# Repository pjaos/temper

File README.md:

# Temper

A Python tool for discovering temperature and humidity sensor units on the local LAN, recording their readings to a SQLite database, and visualising the data through a web-based dashboard.

---

## Overview

Temper consists of two programs that work together along with the ESP32 based hardware.

- **`temper_db`** — a background collector that listens for sensor broadcasts on the LAN and saves every reading to a local SQLite database.
- **`temper_gui`** — a browser-based dashboard (built with [NiceGUI](https://nicegui.io) and [Plotly](https://plotly.com/python/)) for plotting temperature and humidity data across any time range.

The two programs are independent. `temper_db` can run continuously as a background service while `temper_gui` is started on demand to view the data.

---

## Hardware

Temper is designed to work with TEMPER-branded sensor units that broadcast JSON payloads over UDP on the local network. Each unit reports up to four independent temperature/humidity sensor channels, along with system telemetry (RAM, disk, uptime, RSSI, battery voltage, etc.).

Details of the hardware including kicad schematic, PCB and BOM can be found in the hardware folder.

This hardware runs a micropython program which can be found in software/mcu folder. It listens on **UDP port 2934** and responds to *Are You There* broadcast messages with the status (temperature/humidity etc).

---

## Requirements

- Python 3.10 or later

---

## Installation

The python wheel installer file can be found in the linux folder.

### Using the bundled installer

```bash
python3 install.py linux/temper-<version>-py3-none-any.whl
```

This creates a virtual environment, installs all dependencies, and adds the `temper_db` and `temper_gui` commands to your PATH. A temper_gui launch icon is also added to you desktop.

---

## Usage

### Collector — `temper_db`

Discovers TEMPER hardware units on the local LAN and writes every received reading to the database.

```bash
python -m temper.temper_db [options]
```

| Option | Description |
|---|---|
| `-d`, `--debug` | Enable debug logging (prints each received JSON payload). |
| `-a ADDRESS`, `--address ADDRESS` | Only record data from the unit at this IP address. If omitted, all units found are recorded. |
| `-s SECONDS`, `--seconds SECONDS` | Interval between *Are You There* broadcasts (default: 10 s). |
| `--enable_auto_start` | Register the tool to start on system boot |
| `--disable_auto_start` | Un-register the tool to start on system boot |
| `--check_auto_start` | Check the running status |

**Example — record all units, broadcast every 30 seconds:**

```bash
temper_db --seconds 30
```

**Example — record only one unit:**

```bash
temper_db --address 192.168.0.99
```

**Example Running as a service**

Use the built-in boot manager to have the tool start automatically (Linux only):

```bash
temper_db --seconds 30 --enable_auto_start
```

Press **Ctrl-C** to stop.

### Dashboard — `temper_gui`

Starts a local web server and opens the dashboard in the default browser.

```bash
temper_gui [options]
```

| Option | Description |
|---|---|
| `-d`, `--debug` | Enable debug logging. |
| `-p PORT`, `--port PORT` | TCP port for the NiceGUI web server (default: 8085). |
| `-n`, `--no_web_launch` | Start the server without opening a browser tab automatically. |
| `--enable_auto_start` | Register the tool to start on system boot |
| `--disable_auto_start` | Un-register the tool to start on system boot |
| `--check_auto_start` | Check the running status |

**Browser Example**

**Example — start on a non-default port:**

```bash
temper_gui --port 9090
```

**Example — headless server (access from another device):**

```bash
temper_gui --no_web_launch
```

Then navigate to `http://<host-ip>:8085` from any browser on the same network, including a mobile phone.

**Example Running as a service**

Use the built-in boot manager to have the tool start automatically (Linux only):

```bash
temper_gui -n --enable_auto_start
```

---

## Dashboard features

The dashboard is responsive and works on both desktop and mobile browsers.

**Sidebar controls**

- **Units** — chips showing every known unit and its total reading count. Click to select a unit and load its data.
- **Time Range** — preset buttons (1h, 6h, 24h, 7 days, 30 days, All) plus a Custom option with date pickers.
- **Plot** — switch between Temperature and Humidity views.
- **Sensor Names** — rename each of the four sensor channels (e.g. *Living Room*, *Loft*, *Outside*). Names are saved to `sensor_names.json` and persist across restarts. The chart legend and stat tiles update immediately on save.

**Main area**

- **Latest Reading** — a tile grid showing the most recent temperature and humidity value for each active sensor on the selected unit.
- **Chart** — an interactive Plotly time-series plot. Hover over any point to see values for all sensors at that timestamp. Zoom and pan with standard Plotly controls.

---

## Data storage

The database and sensor name configuration are stored in:

| Platform | Path |
|---|---|
| Linux / macOS (XDG) | `~/.config/temper/` |
| Linux / macOS (fallback) / Windows | `~/.temper/` |

Files created:

| File | Contents |
|---|---|
| `temper_sensor_data.db` | SQLite database containing all sensor readings. |
| `sensor_names.json` | User-defined display names for the four sensor channels. |

### Database schema

Two tables are used:

**`units`** — one row per discovered device.

| Column | Type | Description |
|---|---|---|
| `id` | INTEGER | Primary key. |
| `unit_name` | TEXT | Unique device identifier (e.g. `TEMPER_DEV`). |
| `device_type` | TEXT | Always `SENSOR` for TEMPER hardware. |
| `product_id` | TEXT | Always `TEMPER`. |
| `ip_address` | TEXT | Last seen IP address. |
| `os` | TEXT | Firmware OS (e.g. `MicroPython`). |
| `group_name` | TEXT | Optional group label from the device. |
| `service_list` | TEXT | Services advertised by the device. |
| `first_seen` | TIMESTAMP | UTC timestamp of first contact. |
| `last_seen` | TIMESTAMP | UTC timestamp of most recent contact. |

**`sensor_readings`** — one row per received broadcast.

| Column | Type | Description |
|---|---|---|
| `id` | INTEGER | Primary key. |
| `unit_id` | INTEGER | Foreign key → `units.id`. |
| `recorded_at` | TIMESTAMP | UTC time the reading was received. |
| `rx_time_secs` | REAL | Unix timestamp from the device itself. |
| `uptime_seconds` | INTEGER | Device uptime in seconds. |
| `sensor_1_temp` … `sensor_4_temp` | REAL | Temperature readings in °C. |
| `sensor_1_humidity` … `sensor_4_humidity` | REAL | Relative humidity readings in %RH. |
| `param_3v3` | REAL | 3.3 V rail voltage. |
| `param_vbat` | REAL | Battery voltage. |
| `param_rssi` | REAL | Wi-Fi signal strength in dBm. |
| `param_board_temp` | REAL | On-board temperature sensor reading. |
| `ram_*`, `disk_*` | INTEGER | RAM and disk usage telemetry. |

### Maintenance

To delete readings older than 90 days from a Python session:

```python
from temper.temper_db import TemperDB
from unittest.mock import MagicMock
db = TemperDB.__new__(TemperDB)
db._uio = MagicMock(); db._options = None
db._db_file = TemperDB.GetDBFile()
deleted = db.prune_readings_older_than(days=90)
print(f"Deleted {deleted} rows")
```

---

## Running tests

Tests use [pytest](https://pytest.org). From the client directory:

```bash
./run_tests.sh
```

The test suite covers all database operations (`TemperDB`) including table creation, unit upsert, reading insertion, time-range filtering, latest-reading queries, and data pruning. No network access or real hardware is required.

---

## Project structure

```
temper/software/client/
├── src/
│   └── temper/
│       ├── temper_db.py        # Collector + database layer
│       └── temper_gui.py       # NiceGUI web dashboard
└── tests/
    └── test_temper_db.py       # pytest test suite
```

---

## Licence

See `LICENSE` in the repository root.

## Author

Paul Austen — [pjaos@gmail.com](mailto:pjaos@gmail.com)

## Acknowledgements

Development of this project was assisted by [Claude](https://claude.ai) (Anthropic's AI assistant),
which contributed to code review, bug identification, test generation, and this documentation.

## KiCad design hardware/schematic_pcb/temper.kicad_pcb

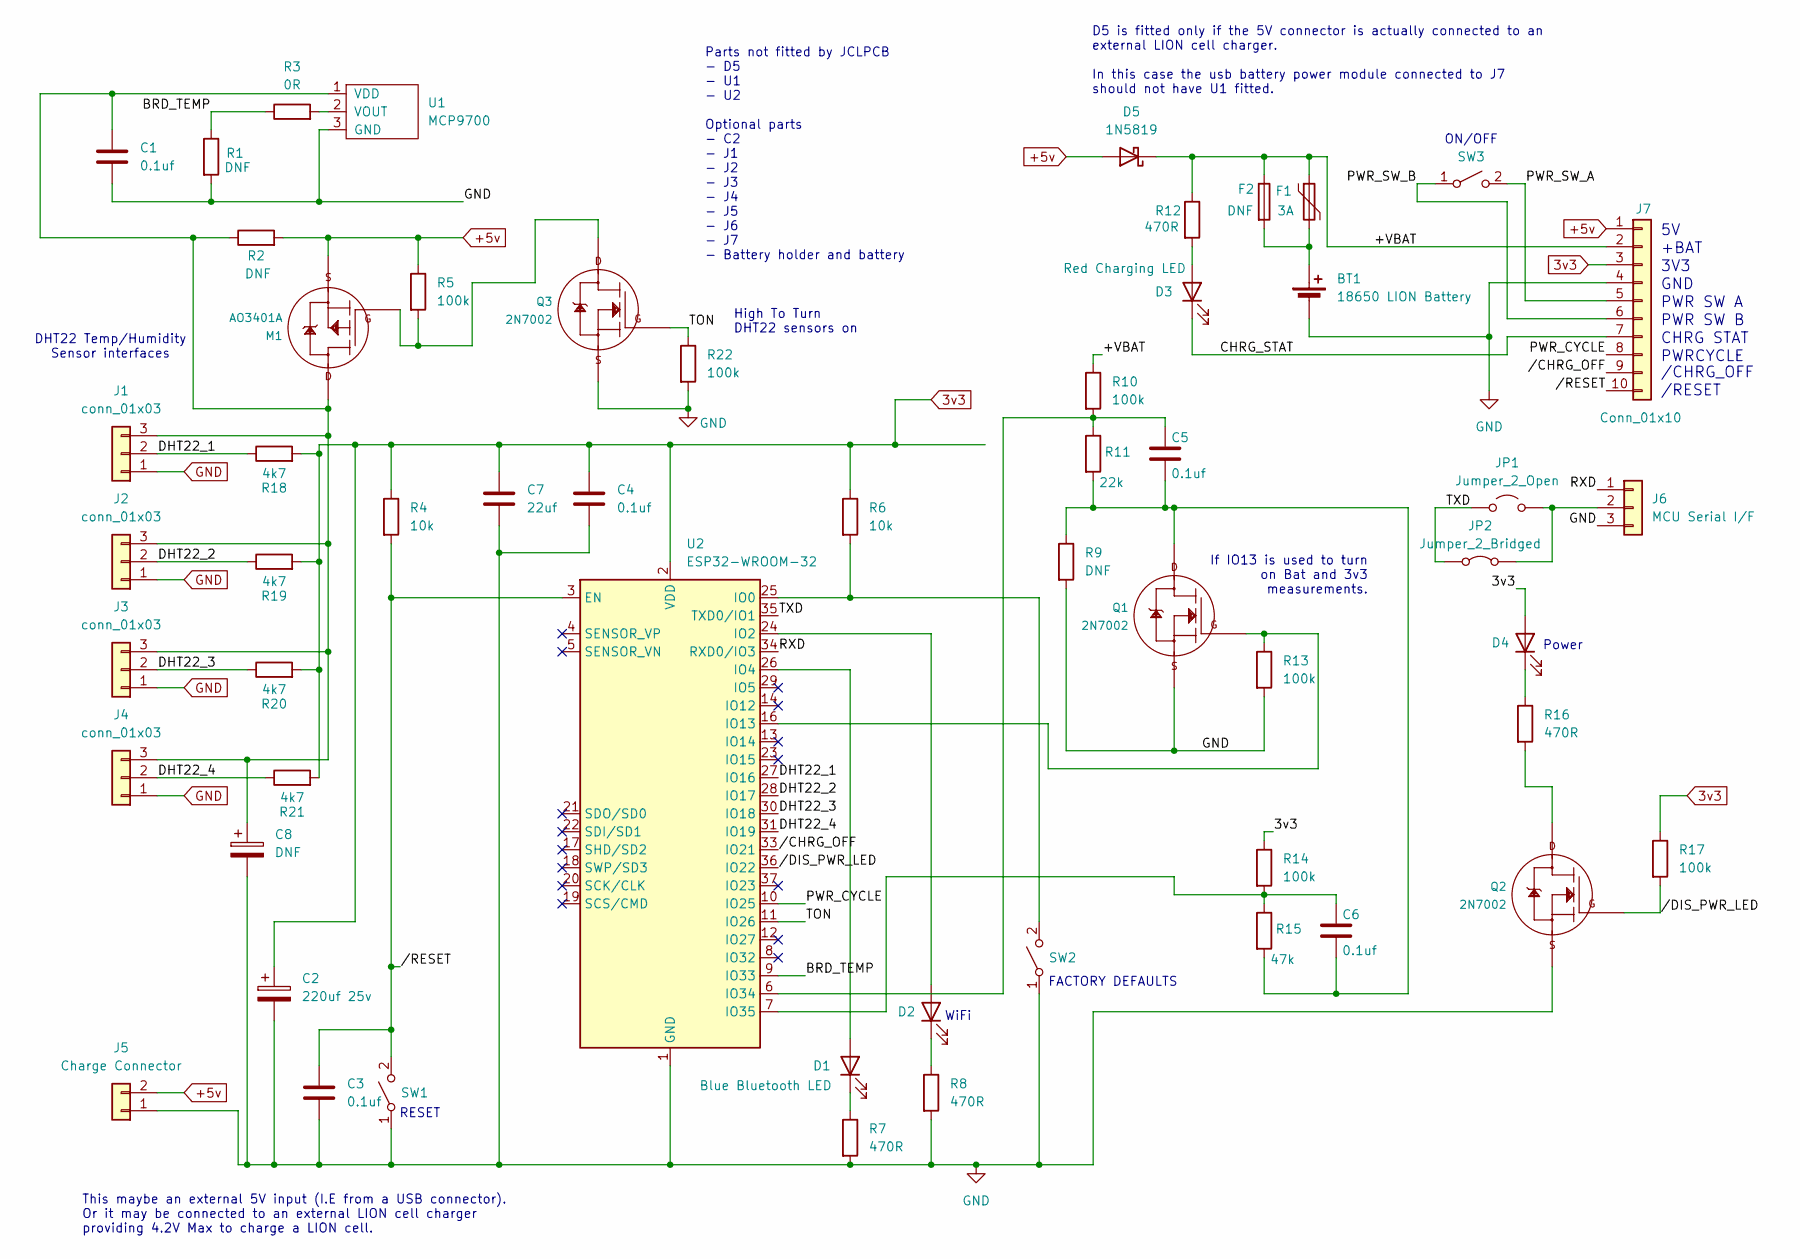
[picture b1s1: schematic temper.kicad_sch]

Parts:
BT1: 18650 LION Battery; 18650_26700_battery_holder
C1, C3, C4, C5, C6: 0.1uf; C_0402_1005Metric_Pad0.74x0.62mm_HandSolder; LCSC C307331
C2: 220uf 25v; CP_Radial_D6.3mm_P2.50mm
C7: 22uf; C_1206_3216Metric_Pad1.33x1.80mm_HandSolder; LCSC C12891
C8: DNF; CP_Radial_D5.0mm_P2.50mm
D1: Blue Bluetooth LED; LED_0805_2012Metric_Pad1.15x1.40mm_HandSolder; LCSC C2296
D2, D4: GreenLED; LED_0805_2012Metric_Pad1.15x1.40mm_HandSolder; LCSC C2297
D3: Red Charging LED; LED_0805_2012Metric_Pad1.15x1.40mm_HandSolder; LCSC C84256
D5: 1N5819; D_SMA_Handsoldering
F1: 3A; PTC_23mm_3mm_10.2mm_wire_spacing
F2: DNF; Scherter_OMT125
J1, J2, J3, J4: conn_01x03; JST_EH_B3B-EH-A_1x03_P2.50mm_Vertical
J5: Charge Connector; JST_EH_B2B-EH-A_1x02_P2.50mm_Vertical
J6: MCU Serial I/F; JST_EH_B3B-EH-A_1x03_P2.50mm_Vertical
J7: Conn_01x10; PinHeader_1x10_P2.54mm_Vertical
JP1: Jumper_2_Open; PinHeader_1x02_P2.54mm_Vertical
JP2: Jumper_2_Bridged; SolderJumper-2_P1.3mm_Bridged_RoundedPad1.0x1.5mm
M1: AO3401A; SOT-23-3; LCSC C15127
Q1, Q2, Q3: 2N7002; SOT-23-3; LCSC C8545
R1, R2, R9: DNF; R_0402_1005Metric_Pad0.72x0.64mm_HandSolder
R3: 0R; R_0402_1005Metric_Pad0.72x0.64mm_HandSolder; LCSC C17168
R4, R6: 10k; R_0402_1005Metric_Pad0.72x0.64mm_HandSolder; LCSC C25744
R5, R10, R13, R14, R17, R22: 100k; R_0402_1005Metric_Pad0.72x0.64mm_HandSolder; LCSC C25741
R7, R8, R12, R16: 470R; R_0402_1005Metric_Pad0.72x0.64mm_HandSolder; LCSC C23179
R11: 22k; R_0402_1005Metric_Pad0.72x0.64mm_HandSolder; LCSC C25768
R15: 47k; R_0402_1005Metric_Pad0.72x0.64mm_HandSolder; LCSC C25792
R18, R19, R20, R21: 4k7; R_0402_1005Metric_Pad0.72x0.64mm_HandSolder; LCSC C25900
SW1, SW2, SW3: tactsw; SW_SPST_SKQG_WithoutStem; LCSC C318884
U1: MCP9700; SOT-23-3
U2: ESP32-WROOM-32

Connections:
3v3: C2.1, C4.1, C7.1, D4.2 (A), J7.3, R4.1, R6.1, R14.1, R17.1, R18.2, R19.2, R20.2, R21.2, U2.2 (VDD)
+5v: D5.2 (A), J5.2, J7.1, M1.2 (S1), R2.2, R5.1
/+VBAT: D5.1 (K), F1.1, F2.1, J7.2, R10.1, R12.1
/BRD_TEMP: R1.1, R3.1, U2.9 (IO33)
/CHRG_STAT: D3.1 (K), J7.7
/DHT22_1: J1.2, R18.1, U2.27 (IO16)
/DHT22_2: J2.2, R19.1, U2.28 (IO17)
/DHT22_3: J3.2, R20.1, U2.30 (IO18)
/DHT22_4: J4.2, R21.1, U2.31 (IO19)
/PWR_CYCLE: J7.8, U2.10 (IO25)
/PWR_SW_A: J7.5, SW3.2 (B)
/PWR_SW_B: J7.6, SW3.1 (A)
/RXD: J6.1, U2.34 (RXD0/IO3)
/TON: Q3.1 (G), R22.1, U2.11 (IO26)
/TXD: JP1.1 (A), JP2.1 (A), U2.35 (TXD0/IO1)
//CHRG_OFF: J7.9, U2.33 (IO21)
//DIS_PWR_LED: Q2.1 (G), R17.2, U2.36 (IO22)
//RESET: C3.1, J7.10, R4.2, SW1.2 (B), U2.3 (EN)
GND: BT1.2 (-), C1.2, C2.2, C3.2, C4.2, C7.2, C8.2, J1.1, J2.1, J3.1, J4.1, J5.1, J6.3, J7.4, Q1.2 (S), Q2.2 (S), Q3.2 (S), R1.2, R7.2, R8.2, R9.2, R13.2, R22.2, SW1.1 (A), SW2.1 (A), U1.3 (GND), U2.1 (GND), U2.15 (GND), U2.38 (GND), U2.39 (GND)
unnamed: BT1.1 (+), F1.2, F2.2
unnamed: D1.2 (A), U2.26 (IO4)
unnamed: D1.1 (K), R7.1
unnamed: D2.2 (A), U2.24 (IO2)
unnamed: D2.1 (K), R8.1
unnamed: D3.2 (A), R12.2
unnamed: D4.1 (K), R16.1
unnamed: C1.1, C8.1, J1.3, J2.3, J3.3, J4.3, M1.3 (D1), R2.1, U1.1 (VDD)
unnamed: J6.2, JP1.2 (B), JP2.2 (B)
unnamed: M1.1 (G1), Q3.3 (D), R5.2
unnamed: C5.2, C6.2, Q1.3 (D), R9.1, R11.2, R15.2
unnamed: Q1.1 (G), R13.1, U2.16 (IO13)
unnamed: Q2.3 (D), R16.2
unnamed: R6.2, SW2.2 (B), U2.25 (IO0)
unnamed: R3.2, U1.2 (VOUT)
unnamed: C5.1, R10.2, R11.1, U2.6 (IO34)
unnamed: C6.1, R14.2, R15.1, U2.7 (IO35)

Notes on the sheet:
+BAT
RESET
If IO13 is used to turn on Bat and 3v3 measurements.
CHRG STAT
Parts not fitted by JCLPCB - D5 - U1 - U2 Optional parts - C2 - J1 - J2 - J3 - J4 - J5 - J6 - J7 - Battery holder and battery
/RESET
Power
High To Turn DHT22 sensors on
/CHRG_OFF
This maybe an external 5V input (I.E from a USB connector). Or it may be connected to an external LION cell charger providing 4.2V Max to charge a LION cell.
FACTORY DEFAULTS
GND
PWR SW A
PWR SW B
DHT22 Temp/Humidity Sensor interfaces
ON/OFF
3V3
PWRCYCLE
WiFi
D5 is fitted only if the 5V connector is actually connected to an external LION cell charger. In this case the usb battery power module connected to J7 should not have U1 fitted.

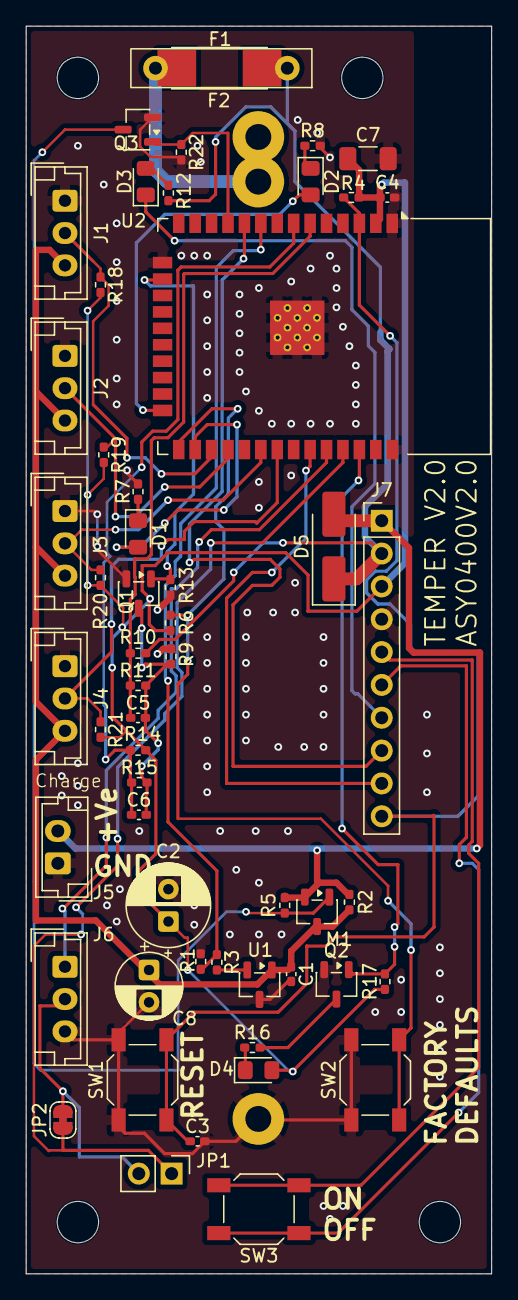
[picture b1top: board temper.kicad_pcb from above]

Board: 2 copper layers, 36.0 x 96.5 mm, 60 parts (0 on the bottom side), 36 nets.

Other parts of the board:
H1, H2, H3, H4: MountingHole_3.2mm_M3

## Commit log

2025-08-25 Add initial schematic/pcb
2025-09-16 First PCB using RPi Pico working
2025-09-19 V1.2 using an ESP32 rather than a RPi Pico W. The ESP32 can handle low power modes better than the RPi Pico W.
2025-10-06 - Move ADC2 pins as ADC2 cannot be used with WiFi. - Add power up reset controller to ensure MCU boots after powercyle event.
2025-10-06 Update to work with v1.2 HW
2025-10-06 Remove remaining mpy files from repo.
2025-10-13 Bump PCB to V1.4 to accept the 26700 Sodium ION battery.
2025-11-10 Add 1.5 HW design.
2026-03-23 Update to add D5.
2026-03-23 Update JCLPCB not fitted parts.
2026-04-06 - Set product ID to TEMPER - Add RSSI to stats - Add board temp to stats - Ensure all connected sensors are read
2026-04-06 Add system params to the stats
2026-04-06 - Add disk size, ram usage and uptime
2026-04-06 Add RSSI call
2026-04-06 Addd new location for 3d printed parts.
2026-04-06 Add starting ppoint for clients to save data to a DB and display this data.
2026-04-06 Ignore the gerbers folder.
2026-04-06 Initial commit where temper_db saves data to sqlite3 db.
2026-04-06 Add poetry lock and ignore files we don't want in the repo.
2026-04-06 Remove empty lines.
2026-04-06 - Fix possible spinlock - Change DB connection timeout from 2 seconds to 30 seconds.
2026-04-06 claud.ai re write to rationailse.
2026-04-06 Add tests for temper_db.py
2026-04-07 Implement a tool to store temper hardware data and another tool to view the data.
2026-04-07 Add an icon for the temper_gui launcher.
2026-04-07 Don't include the cpy of pyproject.toml in the repo.
2026-04-07 Bump to 0.2.0
2026-04-07 Add acknowledgements.
2026-04-07 Add port numbers to sensor ports.
2026-04-07 Add printable file that adds port numbers to case.
2026-04-08 Add updated python wheel
2026-04-08 Add tests for temper_gui.py
2026-04-08 Add top level readme.
2026-04-08 Add MIT license
2026-04-09 Update top to include light pipe for wifi status and button to setup wifi.
2026-04-09 Add dimensions to the Wifi LED and the wifi setup button to the Kicad PCB.
2026-04-09 Add on/off button to case.
2026-04-09 Add location of on/off button to pcb
2026-04-09 Pat watchdog while reading sensors.
2026-04-09 Check factory defaults button every 0.1 seconds
2026-04-09 Change default sensor poll time to once every 60 seconds.
2026-04-09 Add latest python wheel.
2026-04-09 Droip the min pyhon version to 3.10.12
2026-04-10 Display data in localtime not UTC
2026-04-10 Add latest 0.2.2 python wheel.
2026-04-10 - Add sensor read exception text to JSON text for debug purposes. - Make unit name configurable via an http push. - Power cycle sensors when starting MCU SW.
2026-04-10 Add temper_set_name to allow the name of the temper unit to be set. This name is stored inside the temper unit.
2026-04-10 Add ability to delete temper units from the database via the gui.
2026-04-10 Add latest 0.2.4 python wheel installer.
2026-04-11 If we get an error reading the sensors, power cycle the sensor before trying again.
2026-04-11 Enable syslog data for temper_db.py
2026-04-11 - Use p3lib 1.1.158 to get restart service option in boot manager. - Bump version to 0.2.5
2026-04-11 Add latest python wheel installer.
2026-04-11 Added cap on DHT22 power. It's unclear if this is needed and these PCB's have not been built as I'm testing the 1.7 PCB to check if the 220uf 25v cap fixes the sensor read lockup for sensors 2 & 3.
2026-04-11 Change AYT msg so that it is distinct from a standard YView msg.
2026-04-11 Define the AYT msg so that it does not contain the default Yview AYT msg.
2026-04-11 - Revert to org AYT string but use a non Yview UDP port. We now use 2939 ratrher than 2934. - Bump to 0.2.9
2026-04-12 Added an image of the GUI in a web browser window to the readme.
2026-04-15 Add pullup resistors on DHT22 data lines as temp readings were not reliable.
2026-04-24 Spin PCB: Power sensors from 5v (3.3v pullups) to allow sensors to sit on the end of longer cables without locking up.
2026-04-24 Add check for assets folder before creating it.
2026-04-24 Bump p3lib to 1.1.160 to get the cmd line arg to view service log.
2026-04-24 Add cmd line arg to prune database of old records.
2026-04-24 Add cmd limit to the number of records read from the database.
2026-04-24 Add the latest python wheel.
2026-04-24 Stretch the plot accross the browser window width.
2026-04-24 Bump to 0.2.13
2026-05-14 Moved C2 on PCB as there was too close to J5
2026-05-14 - Updated gui so that port names are stored per device. - Bump to 0.2.14
2026-05-14 - Show the IP address of a selected unit in temper_gui.py - Bump to 0.2.15
2026-06-02 Update to kicad v10
2026-06-02 - Apply power to DHT22 for latest HW - When a DHT22 read error occurs record this in the temp and humidity values (=read_error string rather than float value).
2026-06-03 /TON changed to TON for latest SCHEMATIC/PCB
2026-06-03 - Fix incorrect M1 connectivity. - Bump PCB to V2.0
2026-06-03 - Ensure WHL file gets moved to db file at least every hour.
2026-06-03 Ensure sidebar is wide enough to display the X to delete a sensors data if required.
2026-06-03 - Update comments as /TON pin is now TON on latest PCB. - Update 3V3 and 5V rails scale values.
2026-06-03 Bump temper GUI to 0.2.17
2026-06-05 Now the hardware powers off the sensors correctly return to powercycling the DHT22 temperature sensors in the event of a sensor read error.
2026-06-06 - Use latest p3lib to wait for network up on systemd service starts. - Bump to 0.2.18
2026-06-07 - Only try to read connected sensor. During startp a check is made for connected DHT22 temp sensors. Only detected sensors are read. If a sensors fails to read a powercycle occurs to recover the situ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
2026-06-07 - When running temper_db.py ensure the sensor data is logged (if read).
2026-06-07 Bump to 0.2.19
2026-06-08 The follwoing are attempts to stop sensor lockups. - Disable GC during reads, as a gc.collect() during a read may cause DHT22 state machine to lockup. - Add a 1 second delay between each DHT22 device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
2026-06-08 If we read an invalid temperature then raise an error to trigger a power cycle to fix the issue.
2026-06-19 Add workaround for invalid readings, retry followed by reboot.
